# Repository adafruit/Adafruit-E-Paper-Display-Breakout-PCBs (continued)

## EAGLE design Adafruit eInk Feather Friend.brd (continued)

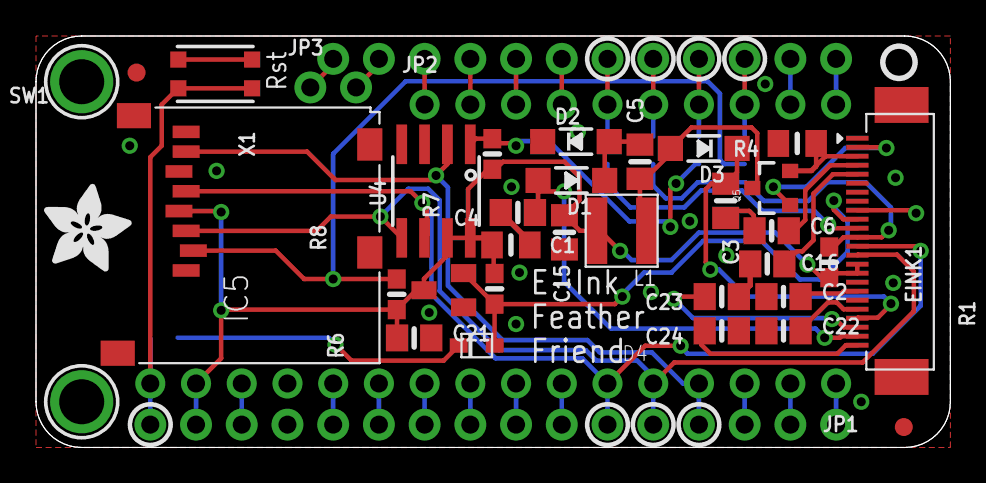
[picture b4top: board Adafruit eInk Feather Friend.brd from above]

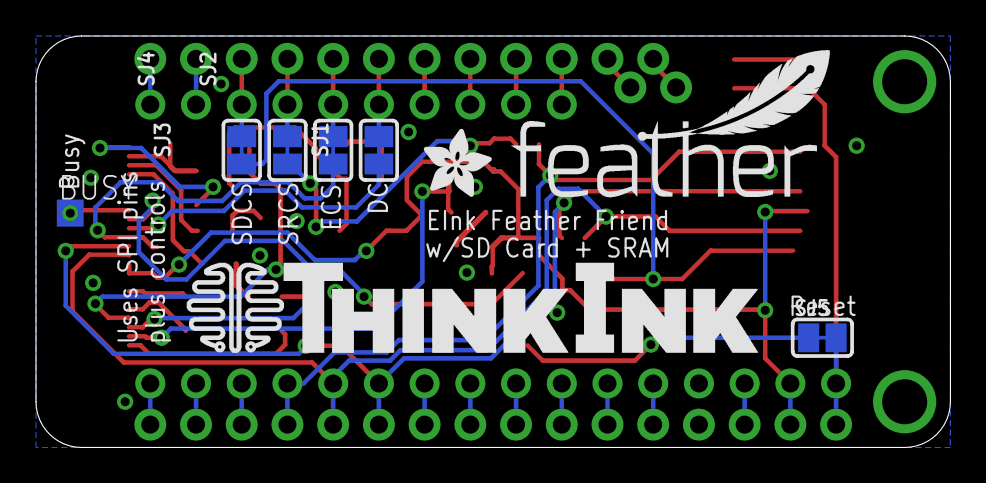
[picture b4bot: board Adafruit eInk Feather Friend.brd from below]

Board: 2 copper layers, 50.8 x 22.9 mm, 47 parts (9 on the bottom side), 47 nets.

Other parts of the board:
U$5: THINKINK_1.25IN
U$6: FEATHERLOGO_MED
U$8: ADAFRUIT_5MM
U$9: PCBFEAT-REV-040
U$17: ADAFRUIT_3.5MM

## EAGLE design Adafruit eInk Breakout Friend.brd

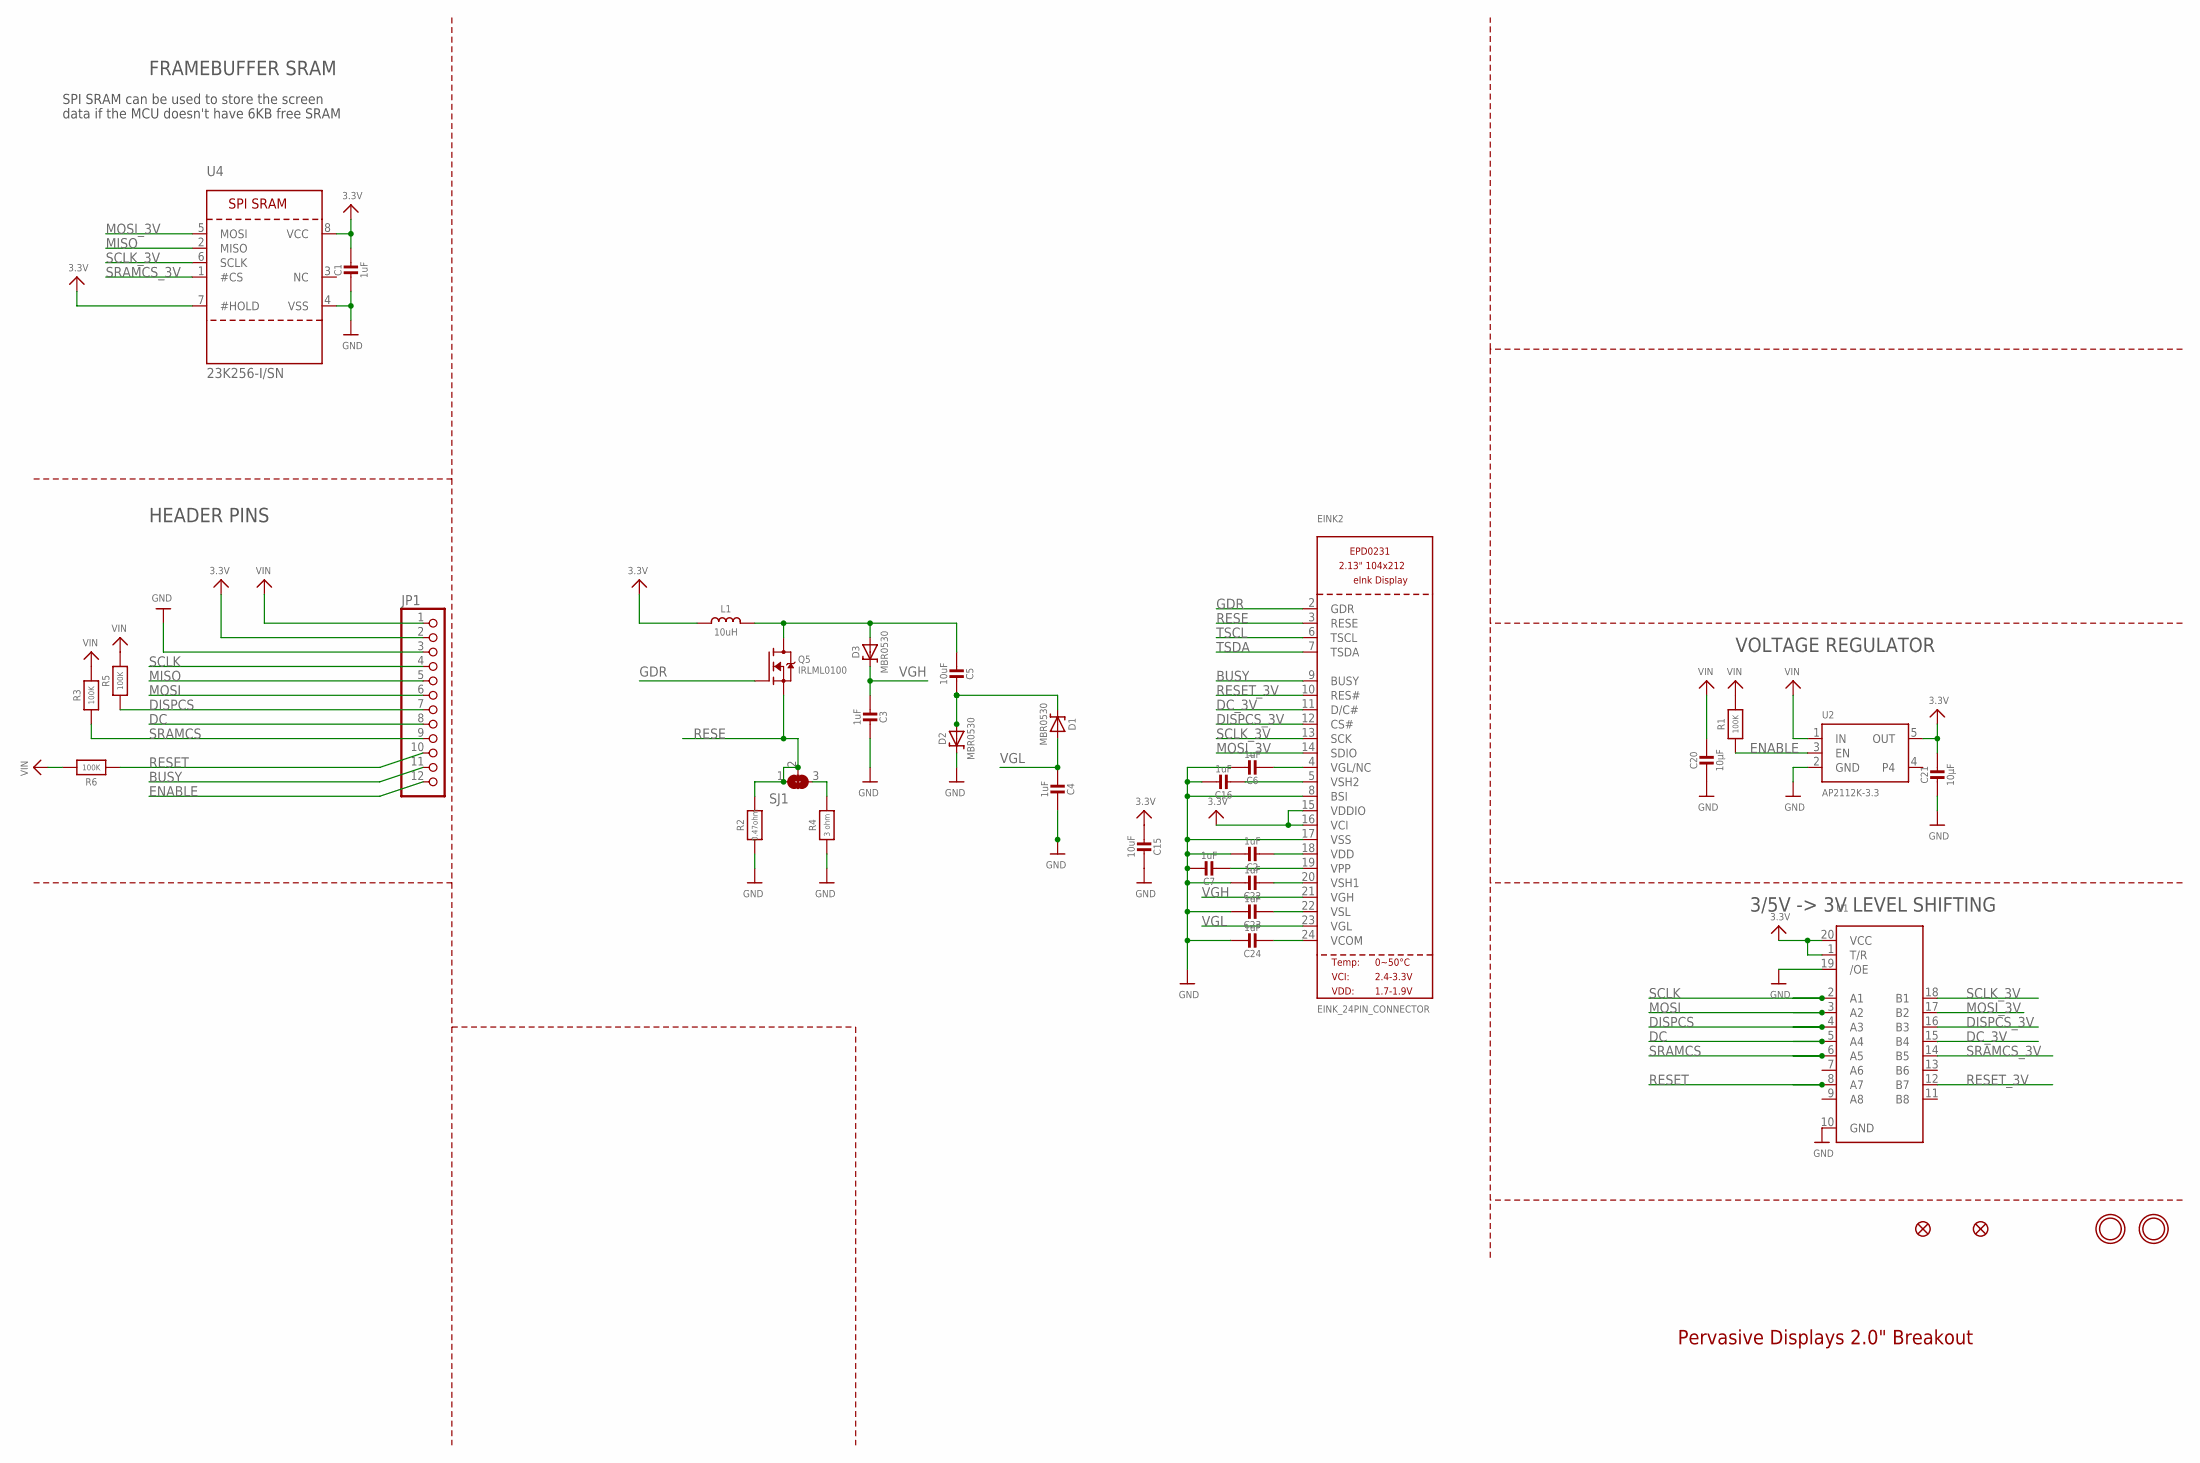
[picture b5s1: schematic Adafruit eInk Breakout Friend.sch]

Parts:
C1: 1uF; 0805_10MGAP
C2, C3, C4, C6, C7, C16, C22, C23, C24: 1uF; 0805-NO
C5, C15: 10uF; 0805-NO
C20, C21: 10µF; 0805-NO
D1, D2, D3: MBR0530; SOD-123
EINK2: EINK_24PIN_CONNECTOR; EINK_24PIN
FID2, FID3: FIDUCIAL_1MM
JP1: HEADER-1X1276MIL; 1X12_ROUND_76MIL
L1: 10uH; INDUCTOR_4X4MM_NR401
Q5: IRLML0100; SOT23-3
R1, R3, R5, R6: 100K; 0603-NO
R2: 0.47ohm; 0805-NO
R4: 3 ohm; 0805-NO
SJ1: SOLDERJUMPER_2WAY; SOLDERJUMPER_2WAY_OPEN_NOPASTE
U1: 74LCX245; TSSOP20
U2: AP2112K-3.3; SOT23-5
U4: 23K256-I/SN; SOIC8_150MIL
U$3, U$4: MOUNTINGHOLE2.5; MOUNTINGHOLE_2.5_PLATED

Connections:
3.3V: C1.1, C15.2, C21.1, EINK2.15 (VDDIO), EINK2.16 (VCI), JP1.2, L1.P$2 (2), U1.1 (T/R), U1.20 (VCC), U2.5 (OUT), U4.7 (#HOLD), U4.8 (VCC)
BUSY: EINK2.9 (BUSY), JP1.11
DC: JP1.8, U1.5 (A4)
DC_3V: EINK2.11 (D/C#), U1.15 (B4)
DISPCS: JP1.7, R5.1, U1.4 (A3)
DISPCS_3V: EINK2.12 (CS#), U1.16 (B3)
ENABLE: JP1.12, R1.1, U2.3 (EN)
GDR: EINK2.2 (GDR), Q5.1 (G)
GND: C1.2, C2.1, C3.2, C4.2, C6.1, C7.1, C15.1, C16.1, C20.2, C21.2, C22.1, C23.1, C24.1, D2.C, EINK2.8 (BSI), EINK2.17 (VSS), JP1.3, R2.2, R4.2, U1.10 (GND), U1.19 (/OE), U2.2 (GND), U4.4 (VSS)
MISO: JP1.5, U4.2 (MISO)
MOSI: JP1.6, U1.3 (A2)
MOSI_3V: EINK2.14 (SDIO), U1.17 (B2), U4.5 (MOSI)
unnamed: C7.2, EINK2.19 (VPP)
unnamed: C5.2, D1.C, D2.A
unnamed: C5.1, D3.A, L1.P$1 (1), Q5.3 (D)
unnamed: C16.2, EINK2.5 (VSH2)
unnamed: C2.2, EINK2.18 (VDD)
unnamed: C22.2, EINK2.20 (VSH1)
unnamed: R4.1, SJ1.3
unnamed: C6.2, EINK2.4 (VGL/NC)
unnamed: C23.2, EINK2.22 (VSL)
unnamed: C24.2, EINK2.24 (VCOM)
RESE: EINK2.3 (RESE), Q5.2 (S), R2.1, SJ1.1, SJ1.2
RESET: JP1.10, R6.1, U1.8 (A7)
RESET_3V: EINK2.10 (RES#), U1.12 (B7)
SCLK: JP1.4, U1.2 (A1)
SCLK_3V: EINK2.13 (SCK), U1.18 (B1), U4.6 (SCLK)
SRAMCS: JP1.9, R3.1, U1.6 (A5)
SRAMCS_3V: U1.14 (B5), U4.1 (#CS)
TSCL: EINK2.6 (TSCL)
TSDA: EINK2.7 (TSDA)
VGH: C3.1, D3.C, EINK2.21 (VGH)
VGL: C4.1, D1.A, EINK2.23 (VGL)
VIN: C20.1, JP1.1, R1.2, R3.2, R5.2, R6.2, U2.1 (IN)

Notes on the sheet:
Pervasive Displays 2.0" Breakout
VOLTAGE REGULATOR
3/5V -> 3V LEVEL SHIFTING
HEADER PINS
FRAMEBUFFER SRAM
SPI SRAM can be used to store the screen
data if the MCU doesn't have 6KB free SRAM

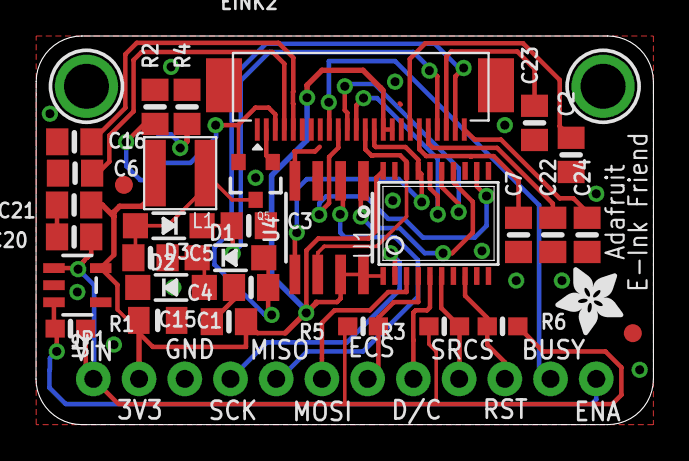
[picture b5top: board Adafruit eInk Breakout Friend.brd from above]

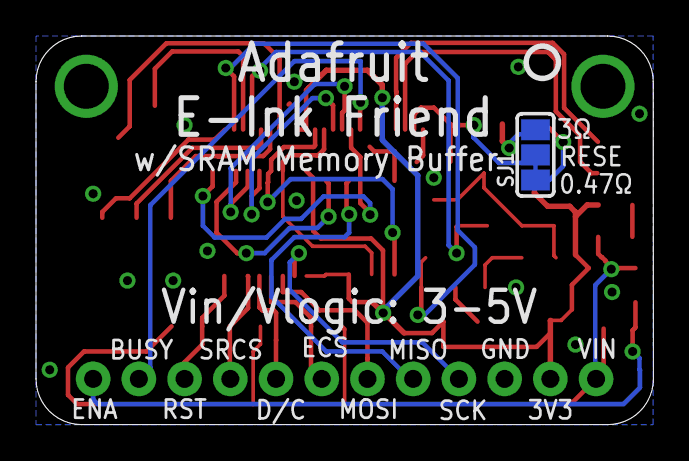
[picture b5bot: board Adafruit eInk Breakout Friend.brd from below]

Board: 2 copper layers, 34.3 x 21.6 mm, 37 parts (2 on the bottom side), 32 nets.

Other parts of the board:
U$2: ADAFRUIT_3.5MM
U$9: PCBFEAT-REV-040

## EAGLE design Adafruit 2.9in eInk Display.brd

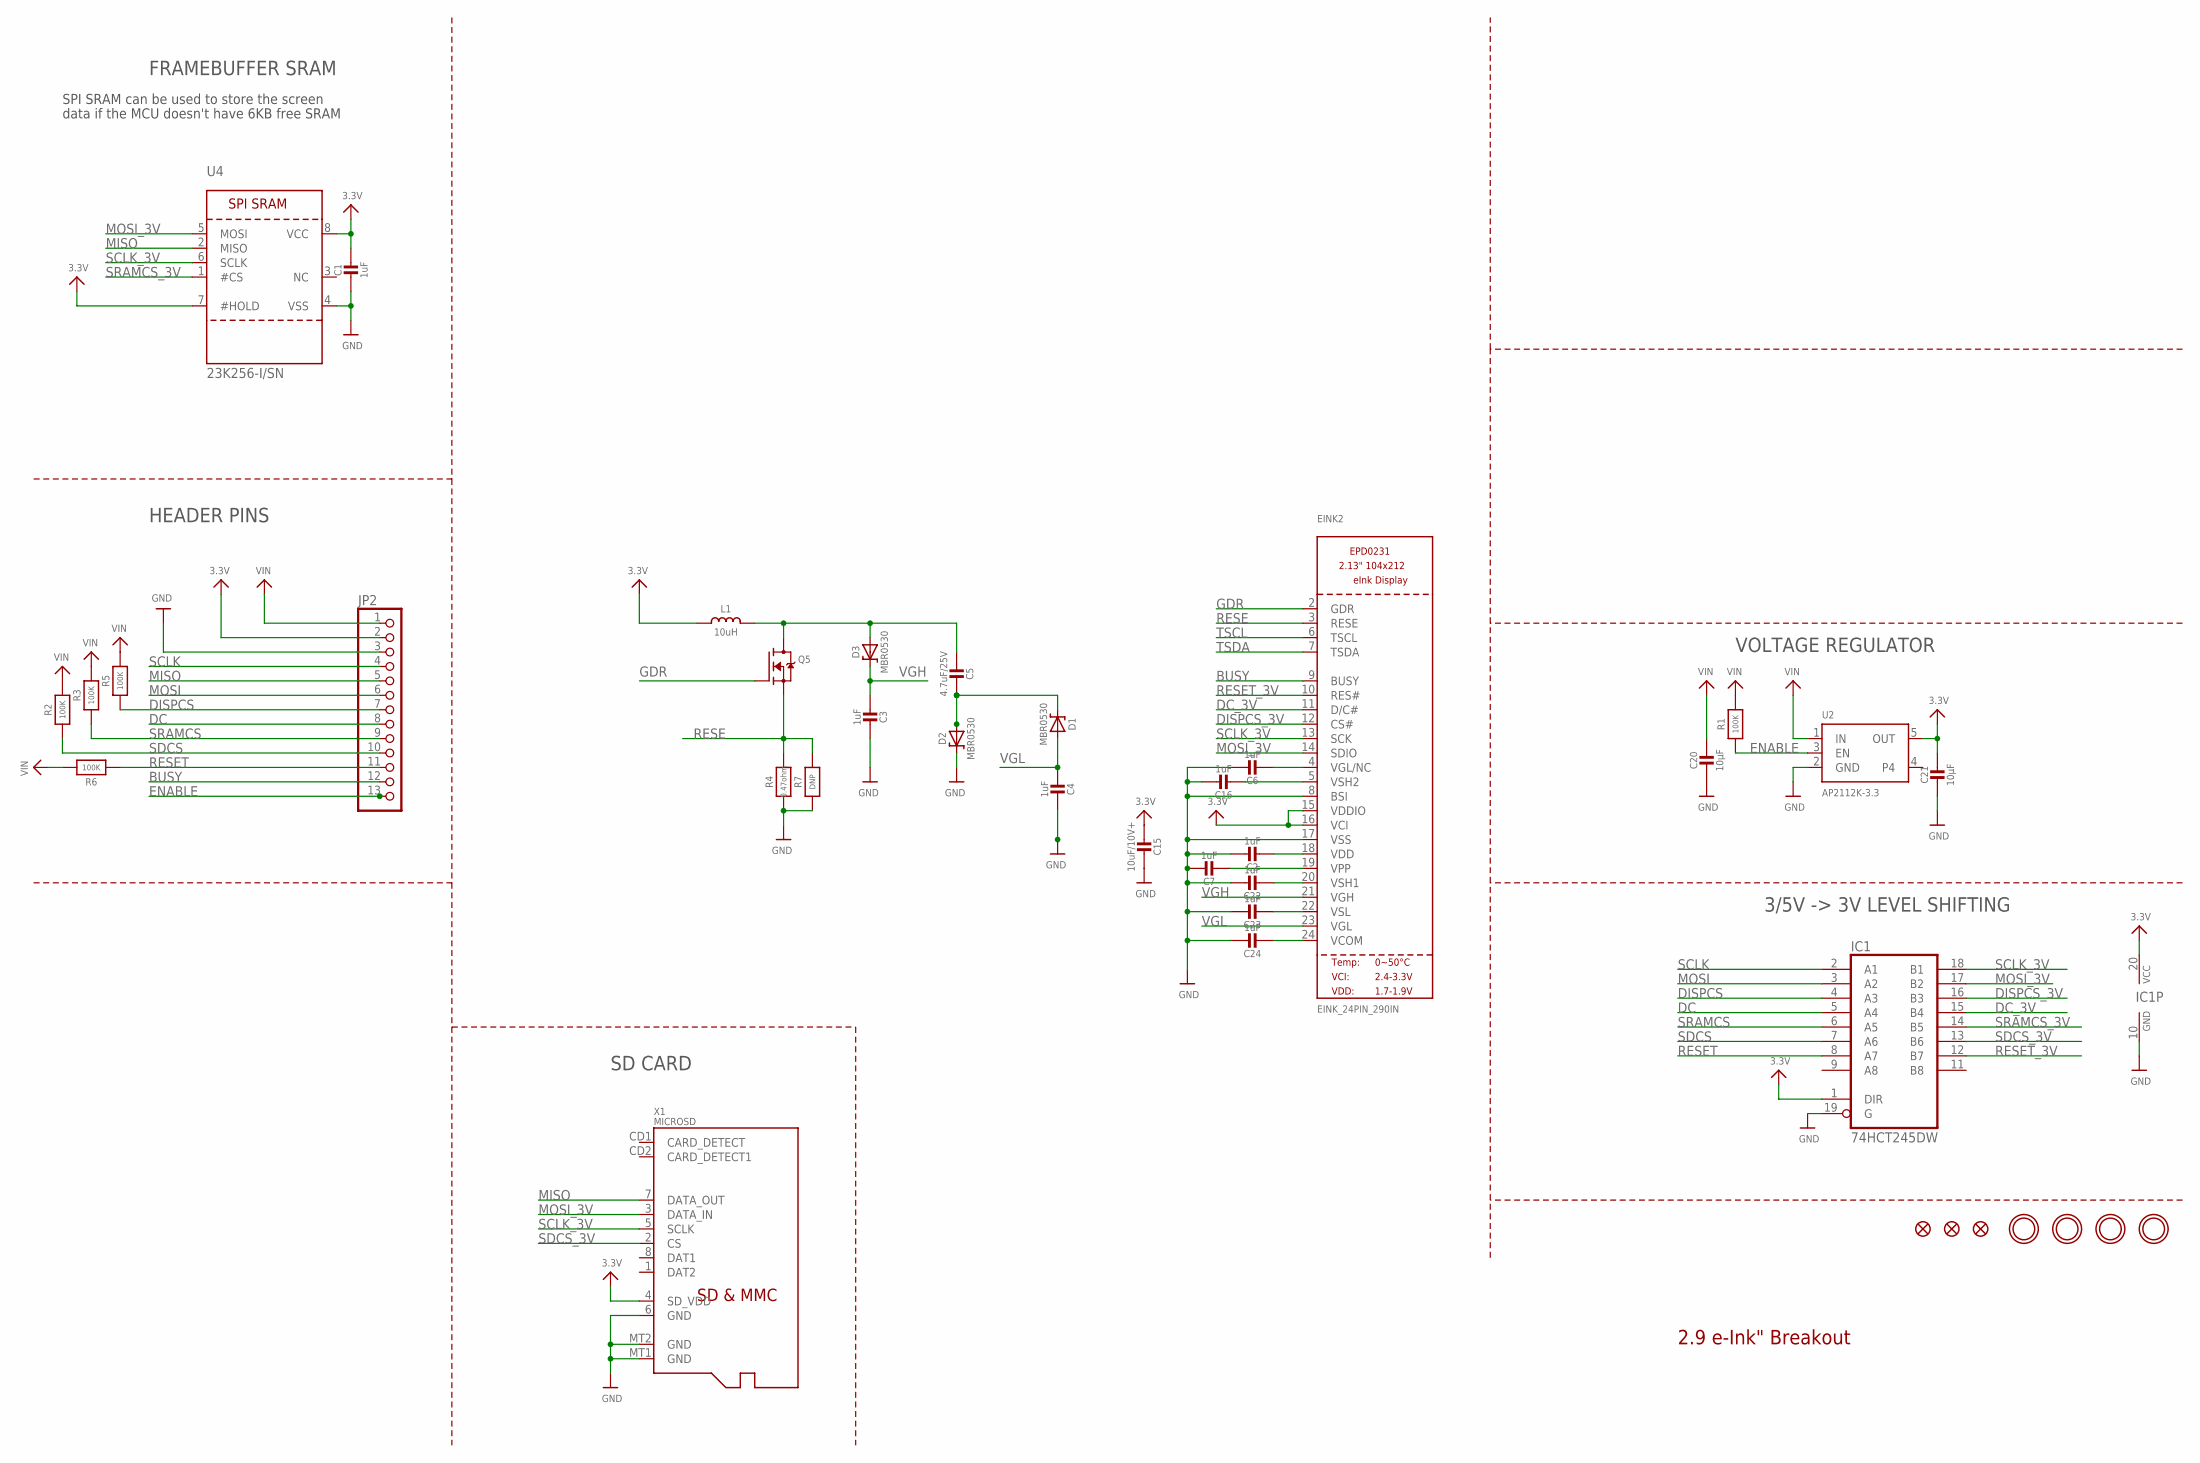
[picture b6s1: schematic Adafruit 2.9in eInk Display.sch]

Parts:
C1: 1uF; 0805_10MGAP
C2, C3, C4, C6, C7, C16, C22, C23, C24: 1uF; 0805-NO
C5: 4.7uF/25V; 0805-NO
C15: 10uF/10V+; 0805-NO
C20, C21: 10µF; 0805-NO
D1, D2, D3: MBR0530; SOD-123
EINK2: EINK_24PIN_290IN; EINK_290IN
FID1, FID2, FID3: FIDUCIAL_1MM
IC1: 74HCT245DW; SO20W
JP2: HEADER-1X13; 1X13_ROUND_70
L1: 10uH; INDUCTOR_4X4MM_NR401
Q5: IRLML0100; SOT23-3
R1, R2, R3, R5, R6: 100K; 0805-NO
R4: 0.47ohm; 0805_10MGAP
R7: DNP; 0805_10MGAP
U2: AP2112K-3.3; SOT23-5
U4: 23K256-I/SN; SOIC8_150MIL
U$3, U$4, U$5, U$6: MOUNTINGHOLE2.5; MOUNTINGHOLE_2.5_PLATED
X1: MICROSD

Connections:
3.3V: C1.1, C15.2, C21.1, EINK2.15 (VDDIO), EINK2.16 (VCI), IC1.1 (DIR), IC1.20 (VCC), JP2.2, L1.P$2 (2), U2.5 (OUT), U4.7 (#HOLD), U4.8 (VCC), X1.4 (SD_VDD)
BUSY: EINK2.9 (BUSY), JP2.12
DC: IC1.5 (A4), JP2.8
DC_3V: EINK2.11 (D/C#), IC1.15 (B4)
DISPCS: IC1.4 (A3), JP2.7, R5.1
DISPCS_3V: EINK2.12 (CS#), IC1.16 (B3)
ENABLE: JP2.13, R1.1, U2.3 (EN)
GDR: EINK2.2 (GDR), Q5.1 (G)
GND: C1.2, C2.1, C3.2, C4.2, C6.1, C7.1, C15.1, C16.1, C20.2, C21.2, C22.1, C23.1, C24.1, D2.C, EINK2.8 (BSI), EINK2.17 (VSS), IC1.10 (GND), IC1.19 (G), JP2.3, R4.2, R7.2, U2.2 (GND), U4.4 (VSS), X1.6 (GND), X1.MT1 (GND), X1.MT2 (GND)
MISO: JP2.5, U4.2 (MISO), X1.7 (DATA_OUT)
MOSI: IC1.3 (A2), JP2.6
MOSI_3V: EINK2.14 (SDIO), IC1.17 (B2), U4.5 (MOSI), X1.3 (DATA_IN)
unnamed: C7.2, EINK2.19 (VPP)
unnamed: C5.2, D1.C, D2.A
unnamed: C5.1, D3.A, L1.P$1 (1), Q5.3 (D)
unnamed: C16.2, EINK2.5 (VSH2)
unnamed: C2.2, EINK2.18 (VDD)
unnamed: C22.2, EINK2.20 (VSH1)
unnamed: C6.2, EINK2.4 (VGL/NC)
unnamed: C23.2, EINK2.22 (VSL)
unnamed: C24.2, EINK2.24 (VCOM)
RESE: EINK2.3 (RESE), Q5.2 (S), R4.1, R7.1
RESET: IC1.8 (A7), JP2.11, R6.1
RESET_3V: EINK2.10 (RES#), IC1.12 (B7)
SCLK: IC1.2 (A1), JP2.4
SCLK_3V: EINK2.13 (SCK), IC1.18 (B1), U4.6 (SCLK), X1.5 (SCLK)
SDCS: IC1.7 (A6), JP2.10, R2.1
SDCS_3V: IC1.13 (B6), X1.2 (CS)
SRAMCS: IC1.6 (A5), JP2.9, R3.1
SRAMCS_3V: IC1.14 (B5), U4.1 (#CS)
TSCL: EINK2.6 (TSCL)
TSDA: EINK2.7 (TSDA)
VGH: C3.1, D3.C, EINK2.21 (VGH)
VGL: C4.1, D1.A, EINK2.23 (VGL)
VIN: C20.1, JP2.1, R1.2, R2.2, R3.2, R5.2, R6.2, U2.1 (IN)

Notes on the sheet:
2.9 e-Ink" Breakout
VOLTAGE REGULATOR
3/5V -> 3V LEVEL SHIFTING
HEADER PINS
FRAMEBUFFER SRAM
SPI SRAM can be used to store the screen
data if the MCU doesn't have 6KB free SRAM
SD CARD

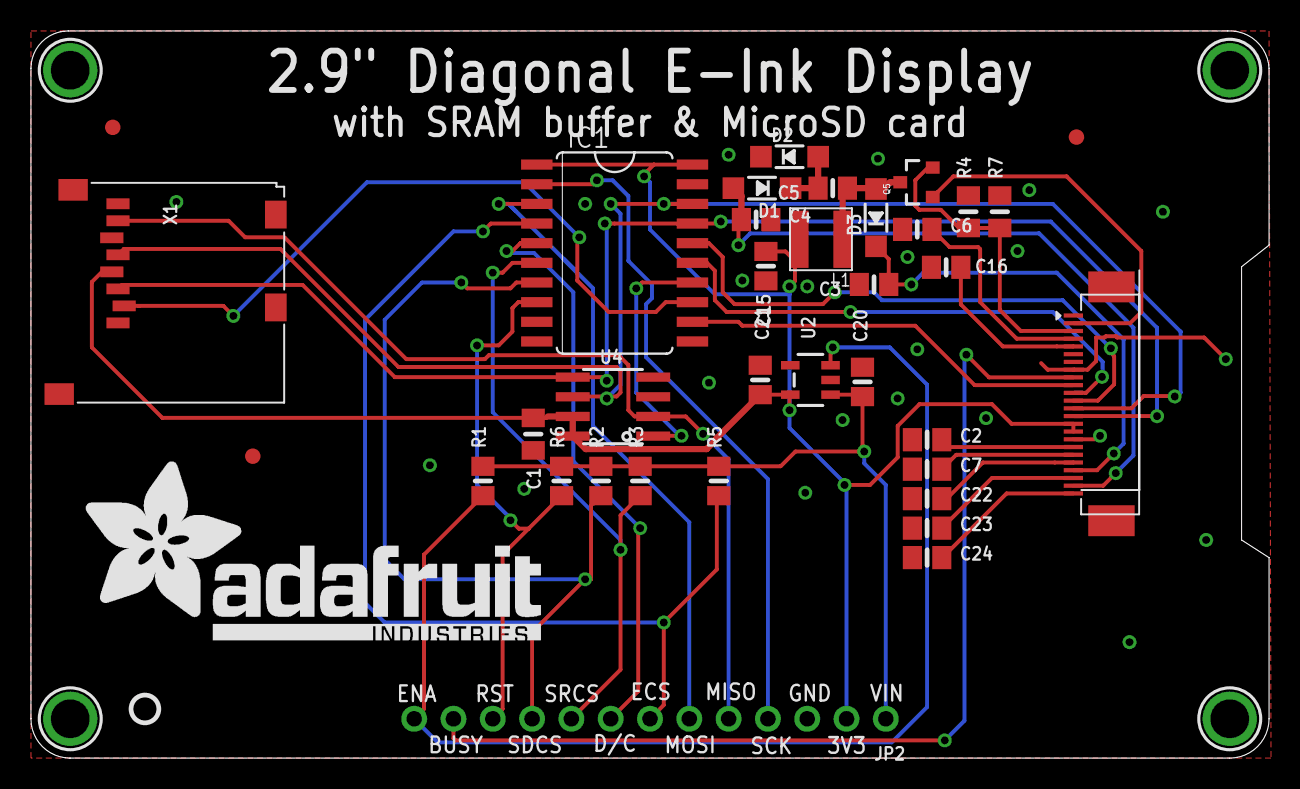
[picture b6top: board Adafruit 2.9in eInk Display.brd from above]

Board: 2 copper layers, 80.0 x 47.0 mm, 41 parts (1 on the bottom side), 33 nets.

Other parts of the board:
U$9: PCBFEAT-REV-040
U$39: ADAFRUIT_TEXT_30MM

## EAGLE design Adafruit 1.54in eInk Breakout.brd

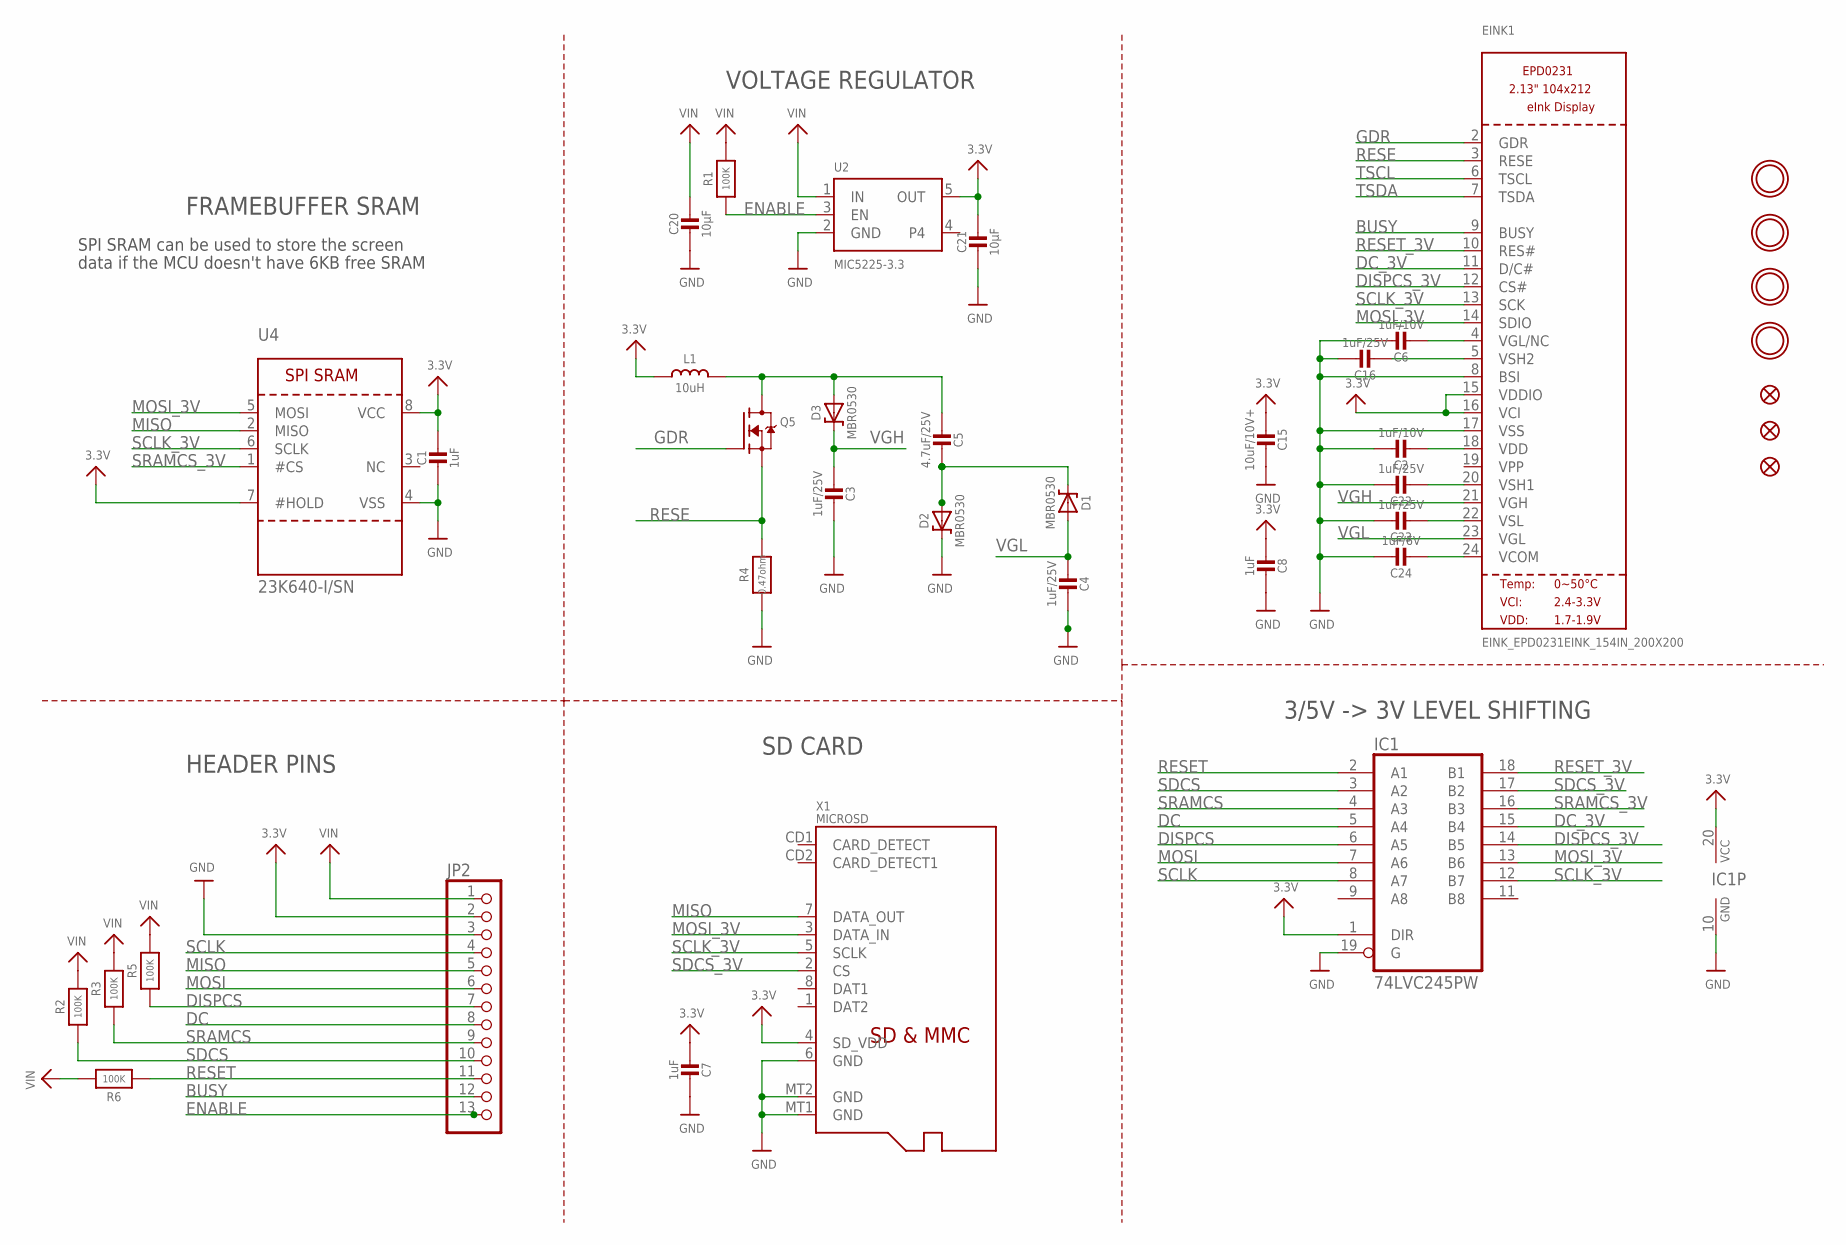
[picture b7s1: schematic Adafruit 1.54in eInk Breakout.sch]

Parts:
C1: 1uF; 0805_10MGAP
C2, C6: 1uF/10V; 0805-NO
C3, C4, C16, C22, C23: 1uF/25V; 0805-NO
C5: 4.7uF/25V; 0805-NO
C7, C8: 1uF; 0805-NO
C15: 10uF/10V+; 0805-NO
C20, C21: 10µF; 0805-NO
C24: 1uF/6V; 0805-NO
D1, D2, D3: MBR0530; SOD-123
EINK1: EINK_EPD0231EINK_154IN_200X200; EINK_154IN
FID1, FID2, FID3: FIDUCIAL_1MM
IC1: 74LVC245PW; TSSOP20
JP2: HEADER-1X13; 1X13_ROUND_70
L1: 10uH; INDUCTOR_4X4MM_NR401
Q5: IRLML0100; SOT23-3
R1, R2, R3, R5, R6: 100K; 0805-NO
R4: 0.47ohm; 0805_10MGAP
U2: MIC5225-3.3; SOT23-5
U4: 23K640-I/SN; SOIC8_150MIL
U$3, U$4, U$5, U$6: MOUNTINGHOLE2.5; MOUNTINGHOLE_2.5_PLATED
X1: MICROSD

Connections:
3.3V: C1.1, C7.1, C8.1, C15.2, C21.1, EINK1.15 (VDDIO), EINK1.16 (VCI), IC1.1 (DIR), IC1.20 (VCC), JP2.2, L1.P$2 (2), U2.5 (OUT), U4.7 (#HOLD), U4.8 (VCC), X1.4 (SD_VDD)
BUSY: EINK1.9 (BUSY), JP2.12
DC: IC1.5 (A4), JP2.8
DC_3V: EINK1.11 (D/C#), IC1.15 (B4)
DISPCS: IC1.6 (A5), JP2.7, R5.1
DISPCS_3V: EINK1.12 (CS#), IC1.14 (B5)
ENABLE: JP2.13, R1.1, U2.3 (EN)
GDR: EINK1.2 (GDR), Q5.1 (G)
GND: C1.2, C2.1, C3.2, C4.2, C6.1, C7.2, C8.2, C15.1, C16.1, C20.2, C21.2, C22.1, C23.1, C24.1, D2.C, EINK1.8 (BSI), EINK1.17 (VSS), IC1.10 (GND), IC1.19 (G), JP2.3, R4.2, U2.2 (GND), U4.4 (VSS), X1.6 (GND), X1.MT1 (GND), X1.MT2 (GND)
MISO: JP2.5, U4.2 (MISO), X1.7 (DATA_OUT)
MOSI: IC1.7 (A6), JP2.6
MOSI_3V: EINK1.14 (SDIO), IC1.13 (B6), U4.5 (MOSI), X1.3 (DATA_IN)
unnamed: C5.2, D1.C, D2.A
unnamed: C5.1, D3.A, L1.P$1 (1), Q5.3 (D)
unnamed: C16.2, EINK1.5 (VSH2)
unnamed: C2.2, EINK1.18 (VDD)
unnamed: C22.2, EINK1.20 (VSH1)
unnamed: C6.2, EINK1.4 (VGL/NC)
unnamed: C23.2, EINK1.22 (VSL)
unnamed: C24.2, EINK1.24 (VCOM)
RESE: EINK1.3 (RESE), Q5.2 (S), R4.1
RESET: IC1.2 (A1), JP2.11, R6.1
RESET_3V: EINK1.10 (RES#), IC1.18 (B1)
SCLK: IC1.8 (A7), JP2.4
SCLK_3V: EINK1.13 (SCK), IC1.12 (B7), U4.6 (SCLK), X1.5 (SCLK)
SDCS: IC1.3 (A2), JP2.10, R2.1
SDCS_3V: IC1.17 (B2), X1.2 (CS)
SRAMCS: IC1.4 (A3), JP2.9, R3.1
SRAMCS_3V: IC1.16 (B3), U4.1 (#CS)
TSCL: EINK1.6 (TSCL)
TSDA: EINK1.7 (TSDA)
VGH: C3.1, D3.C, EINK1.21 (VGH)
VGL: C4.1, D1.A, EINK1.23 (VGL)
VIN: C20.1, JP2.1, R1.2, R2.2, R3.2, R5.2, R6.2, U2.1 (IN)

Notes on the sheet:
VOLTAGE REGULATOR
3/5V -> 3V LEVEL SHIFTING
HEADER PINS
FRAMEBUFFER SRAM
SPI SRAM can be used to store the screen
data if the MCU doesn't have 6KB free SRAM
SD CARD

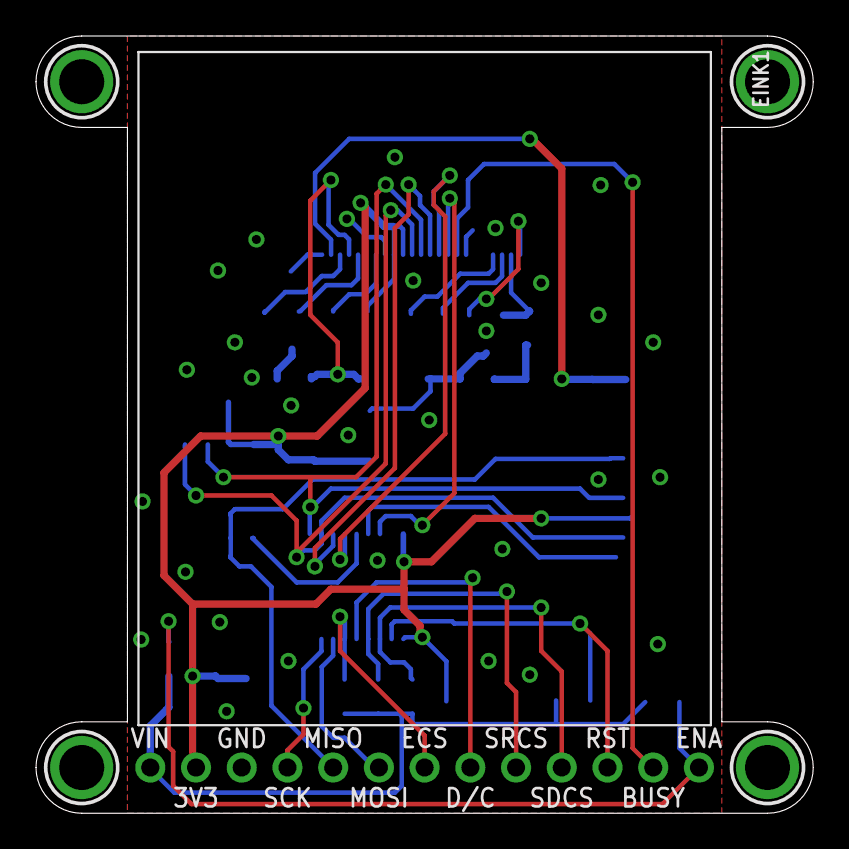
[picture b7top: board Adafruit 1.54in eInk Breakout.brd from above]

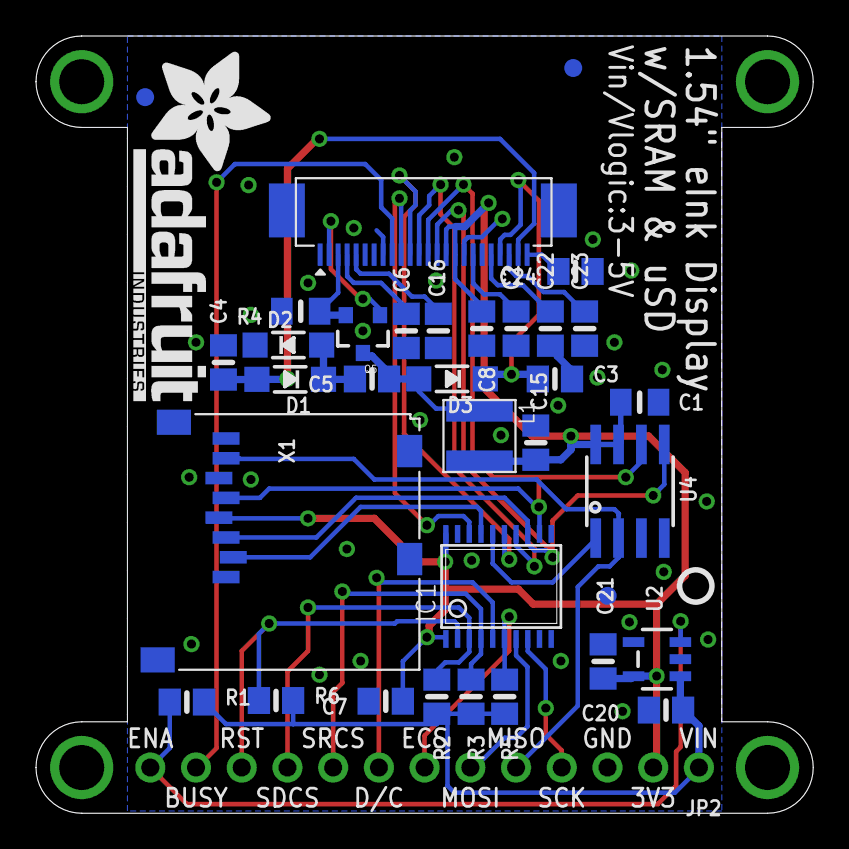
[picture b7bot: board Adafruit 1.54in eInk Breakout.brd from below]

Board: 2 copper layers, 43.2 x 43.2 mm, 41 parts (36 on the bottom side), 32 nets.

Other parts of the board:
U$9: PCBFEAT-REV-040
U$28: ADAFRUIT_TEXT_20MM

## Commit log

2018-07-16 init
2018-07-16 read
2019-02-13 Adding 2.7" and 2.13" PCB files
2019-02-13 Updated with links to 2.13/2.7in displays
2019-08-07 adding 2.13in featherwing
2019-09-13 added 2.9" display
2019-12-19 Adding PCB files for eInk Friends
2020-10-29 Added 2.9 inch eInk FeatherWing
2023-02-21 adding 2.13 EYESPI files
2023-02-21 adding product link to readme
2023-02-21 adding Adafruit to file names
2023-03-31 Adding 2.7" eyespi
2024-02-07 adding 1.54 eink with eyespi
